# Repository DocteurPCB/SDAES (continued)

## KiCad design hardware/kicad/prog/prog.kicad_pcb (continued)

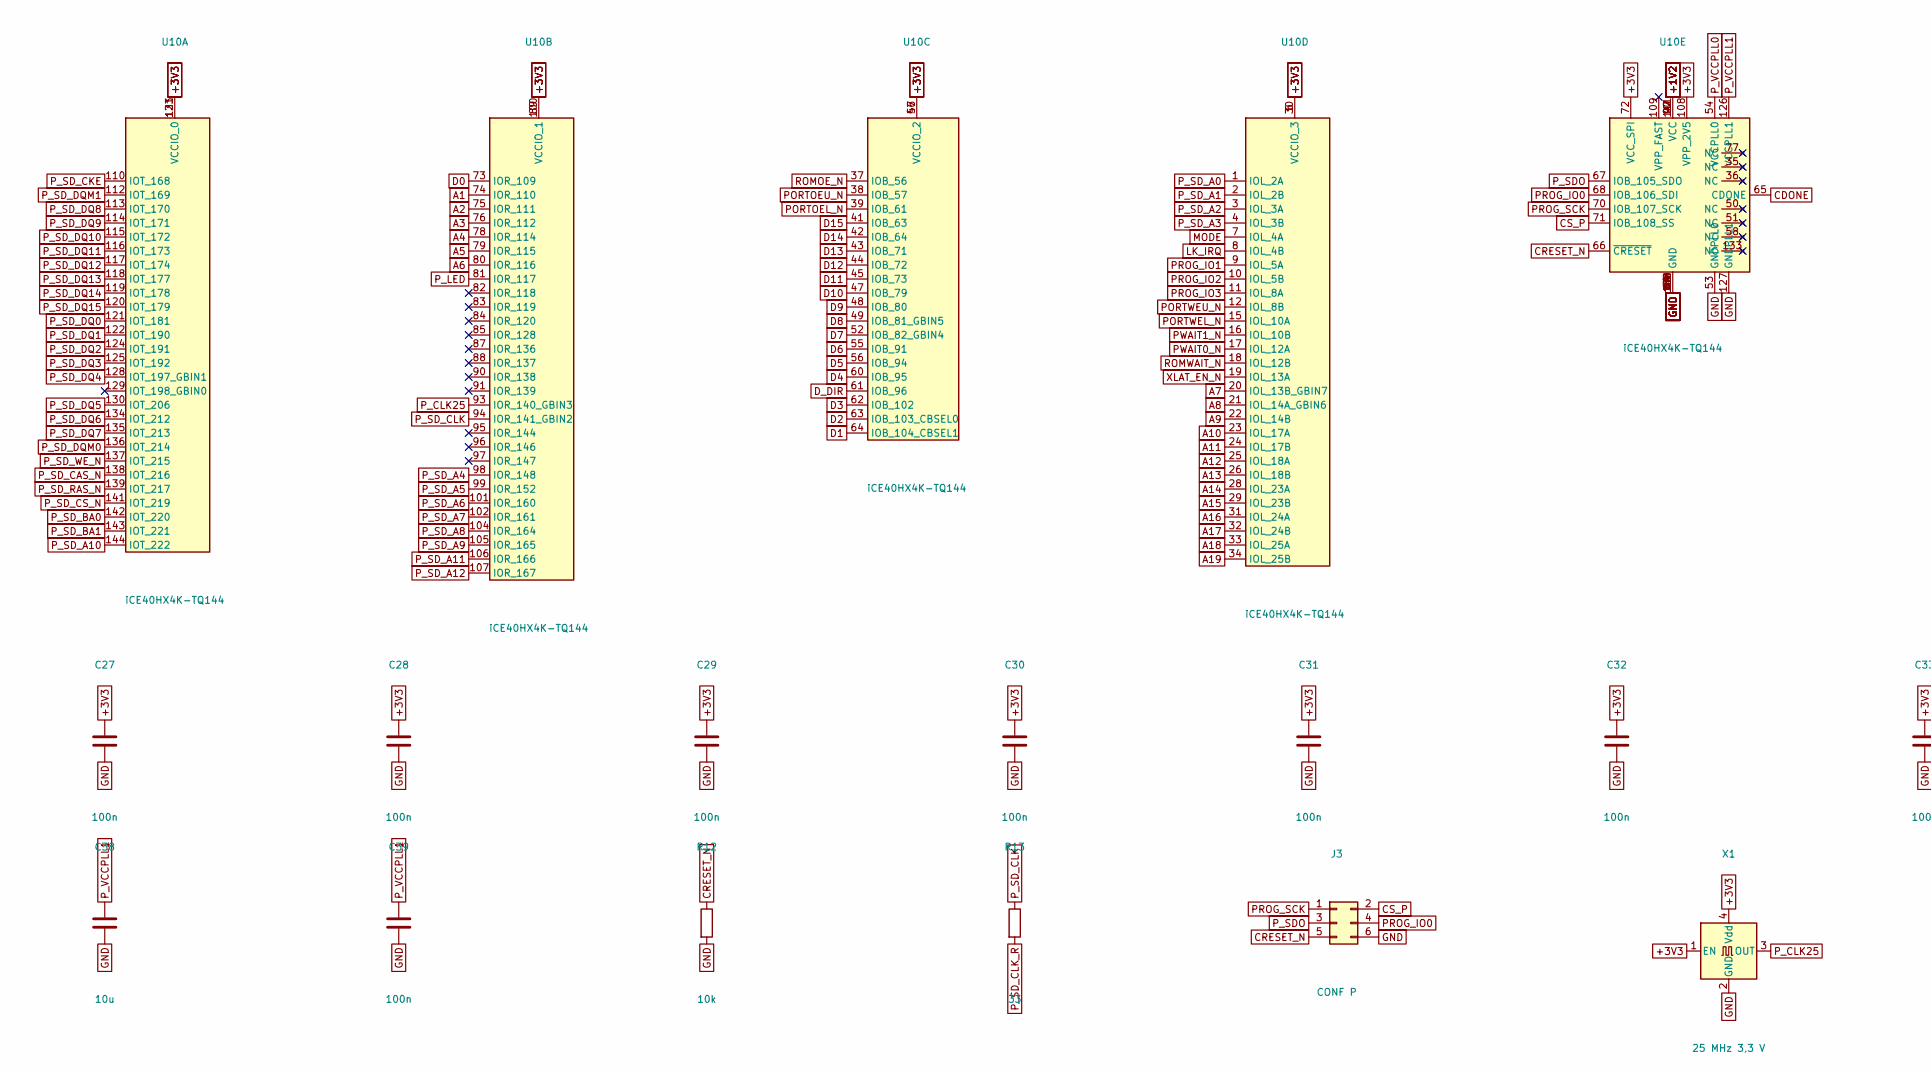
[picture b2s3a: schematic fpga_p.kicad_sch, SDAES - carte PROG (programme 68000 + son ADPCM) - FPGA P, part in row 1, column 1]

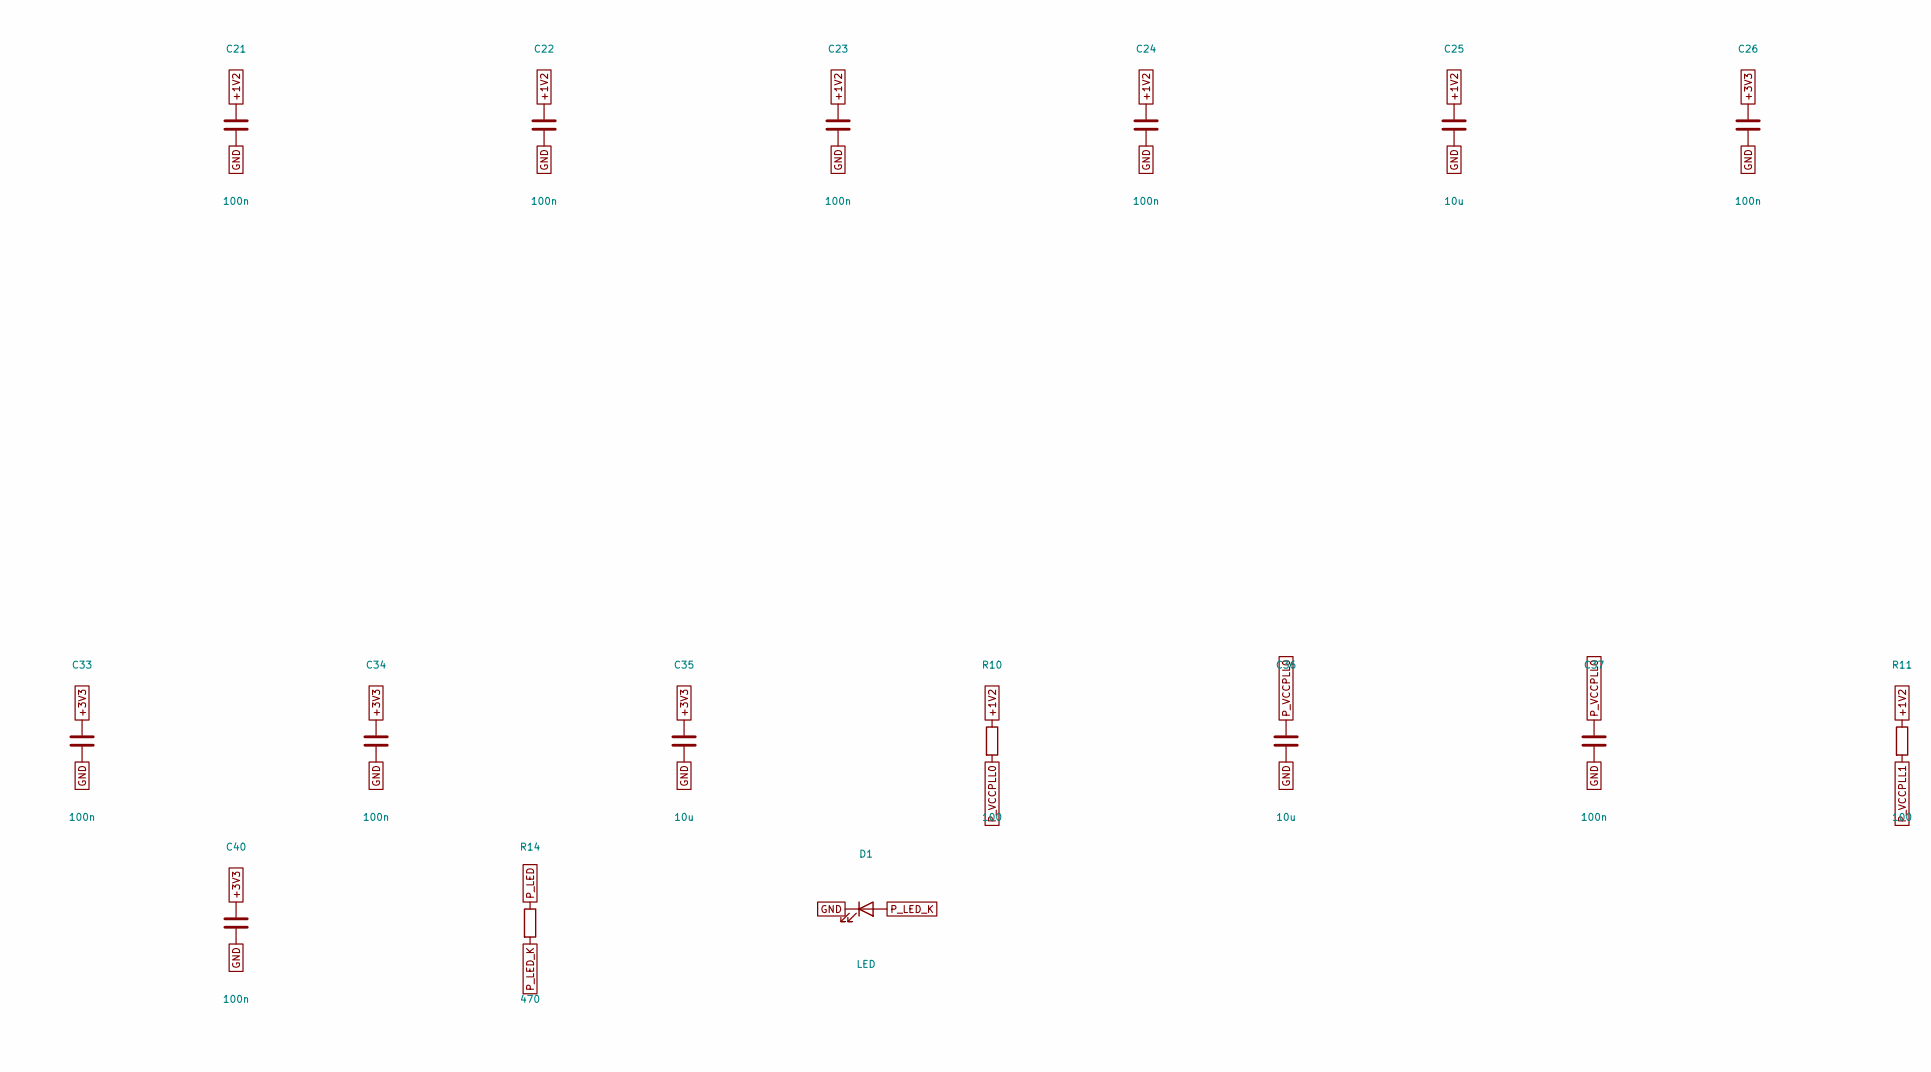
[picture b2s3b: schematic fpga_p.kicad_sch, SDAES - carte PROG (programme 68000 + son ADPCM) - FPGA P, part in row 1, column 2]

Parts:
C21, C22, C23, C24, C26, C27, C28, C29, C30, C31, C32, C33, C34, C37, C39, C40: 100n; C_0603_1608Metric
C25, C35, C36, C38: 10u; C_0805_2012Metric
D1: LED; LED_0603_1608Metric
J3: CONF P; PinHeader_2x03_P2.54mm_Vertical
R10, R11: 100; R_0603_1608Metric
R12: 10k; R_0603_1608Metric
R13: 33; R_0603_1608Metric
R14: 470; R_0603_1608Metric
U10: iCE40HX4K-TQ144; TQFP-144_20x20mm_P0.5mm
X1: 25 MHz 3,3 V; Oscillator_SMD_Abracon_ASE-4Pin_3.2x2.5mm_HandSoldering

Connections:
+1V2: C21.1, C22.1, C23.1, C24.1, C25.1, R10.1, R11.1, U10.27 (VCC), U10.40 (VCC), U10.92 (VCC), U10.111 (VCC); also elsewhere on the board
+3V3: C26.1, C27.1, C28.1, C29.1, C30.1, C31.1, C32.1, C33.1, C34.1, C35.1, C40.1, U10.6 (VCCIO_3), U10.30 (VCCIO_3), U10.46 (VCCIO_2), U10.57 (VCCIO_2), U10.72 (VCC_SPI), U10.89 (VCCIO_1), U10.100 (VCCIO_1), U10.108 (VPP_2V5), U10.123 (VCCIO_0), U10.131 (VCCIO_0), X1.1 (EN), X1.4 (Vdd); also elsewhere on the board
A1: U10.74 (IOR_110); also elsewhere on the board
A2: U10.75 (IOR_111); also elsewhere on the board
A3: U10.76 (IOR_112); also elsewhere on the board
A4: U10.78 (IOR_114); also elsewhere on the board
A5: U10.79 (IOR_115); also elsewhere on the board
A6: U10.80 (IOR_116); also elsewhere on the board
A7: U10.20 (IOL_13B_GBIN7); also elsewhere on the board
A8: U10.21 (IOL_14A_GBIN6); also elsewhere on the board
A9: U10.22 (IOL_14B); also elsewhere on the board
A10: U10.23 (IOL_17A); also elsewhere on the board
A11: U10.24 (IOL_17B); also elsewhere on the board
A12: U10.25 (IOL_18A); also elsewhere on the board
A13: U10.26 (IOL_18B); also elsewhere on the board
A14: U10.28 (IOL_23A); also elsewhere on the board
A15: U10.29 (IOL_23B); also elsewhere on the board
A16: U10.31 (IOL_24A); also elsewhere on the board
A17: U10.32 (IOL_24B); also elsewhere on the board
A18: U10.33 (IOL_25A); also elsewhere on the board
A19: U10.34 (IOL_25B); also elsewhere on the board
CDONE: U10.65 (CDONE); also elsewhere on the board
CRESET_N: J3.5, R12.1, U10.66 (~CRESET); also elsewhere on the board
CS_P: J3.2, U10.71 (IOB_108_SS); also elsewhere on the board
D0: U10.73 (IOR_109); also elsewhere on the board
D1: U10.64 (IOB_104_CBSEL1); also elsewhere on the board
D2: U10.63 (IOB_103_CBSEL0); also elsewhere on the board
D3: U10.62 (IOB_102); also elsewhere on the board
D4: U10.60 (IOB_95); also elsewhere on the board
D5: U10.56 (IOB_94); also elsewhere on the board
D6: U10.55 (IOB_91); also elsewhere on the board
D7: U10.52 (IOB_82_GBIN4); also elsewhere on the board
D8: U10.49 (IOB_81_GBIN5); also elsewhere on the board
D9: U10.48 (IOB_80); also elsewhere on the board
D10: U10.47 (IOB_79); also elsewhere on the board
D11: U10.45 (IOB_73); also elsewhere on the board
D12: U10.44 (IOB_72); also elsewhere on the board
D13: U10.43 (IOB_71); also elsewhere on the board
D14: U10.42 (IOB_64); also elsewhere on the board
D15: U10.41 (IOB_63); also elsewhere on the board
D_DIR: U10.61 (IOB_96); also elsewhere on the board
GND: C21.2, C22.2, C23.2, C24.2, C25.2, C26.2, C27.2, C28.2, C29.2, C30.2, C31.2, C32.2, C33.2, C34.2, C35.2, C36.2, C37.2, C38.2, C39.2, C40.2, D1.1 (K), J3.6, R12.2, U10.5 (GND), U10.13 (GND), U10.14 (GND), U10.53 (GNDPLL0), U10.59 (GND), U10.69 (GND), U10.86 (GND), U10.103 (GND), U10.127 (GNDPLL1), U10.132 (GND), U10.140 (GND), X1.2 (GND); also elsewhere on the board
LK_IRQ: U10.8 (IOL_4B); also elsewhere on the board
MODE: U10.7 (IOL_4A); also elsewhere on the board
PORTOEL_N: U10.39 (IOB_61); also elsewhere on the board
PORTOEU_N: U10.38 (IOB_57); also elsewhere on the board
PORTWEL_N: U10.15 (IOL_10A); also elsewhere on the board
PORTWEU_N: U10.12 (IOL_8B); also elsewhere on the board
PROG_IO0: J3.4, U10.68 (IOB_106_SDI); also elsewhere on the board
PROG_IO1: U10.9 (IOL_5A); also elsewhere on the board
PROG_IO2: U10.10 (IOL_5B); also elsewhere on the board
PROG_IO3: U10.11 (IOL_8A); also elsewhere on the board
PROG_SCK: J3.1, U10.70 (IOB_107_SCK); also elsewhere on the board
PWAIT0_N: U10.17 (IOL_12A); also elsewhere on the board
PWAIT1_N: U10.16 (IOL_10B); also elsewhere on the board
P_CLK25: U10.93 (IOR_140_GBIN3), X1.3 (OUT)
P_LED: R14.1, U10.81 (IOR_117)
P_LED_K: D1.2 (A), R14.2
P_SDO: J3.3, U10.67 (IOB_105_SDO)
P_SD_A0: U10.1 (IOL_2A); also elsewhere on the board
P_SD_A1: U10.2 (IOL_2B); also elsewhere on the board
P_SD_A2: U10.3 (IOL_3A); also elsewhere on the board
P_SD_A3: U10.4 (IOL_3B); also elsewhere on the board
P_SD_A4: U10.98 (IOR_148); also elsewhere on the board
P_SD_A5: U10.99 (IOR_152); also elsewhere on the board
P_SD_A6: U10.101 (IOR_160); also elsewhere on the board
P_SD_A7: U10.102 (IOR_161); also elsewhere on the board
P_SD_A8: U10.104 (IOR_164); also elsewhere on the board
P_SD_A9: U10.105 (IOR_165); also elsewhere on the board
P_SD_A10: U10.144 (IOT_222); also elsewhere on the board
P_SD_A11: U10.106 (IOR_166); also elsewhere on the board
P_SD_A12: U10.107 (IOR_167); also elsewhere on the board
P_SD_BA0: U10.142 (IOT_220); also elsewhere on the board
P_SD_BA1: U10.143 (IOT_221); also elsewhere on the board
P_SD_CAS_N: U10.138 (IOT_216); also elsewhere on the board
P_SD_CKE: U10.110 (IOT_168); also elsewhere on the board
P_SD_CLK: R13.1, U10.94 (IOR_141_GBIN2)
P_SD_CLK_R: R13.2; also elsewhere on the board
P_SD_CS_N: U10.141 (IOT_219); also elsewhere on the board
P_SD_DQ0: U10.121 (IOT_181); also elsewhere on the board
P_SD_DQ1: U10.122 (IOT_190); also elsewhere on the board
P_SD_DQ2: U10.124 (IOT_191); also elsewhere on the board
P_SD_DQ3: U10.125 (IOT_192); also elsewhere on the board
P_SD_DQ4: U10.128 (IOT_197_GBIN1); also elsewhere on the board
P_SD_DQ5: U10.130 (IOT_206); also elsewhere on the board
P_SD_DQ6: U10.134 (IOT_212); also elsewhere on the board
P_SD_DQ7: U10.135 (IOT_213); also elsewhere on the board
P_SD_DQ8: U10.113 (IOT_170); also elsewhere on the board
P_SD_DQ9: U10.114 (IOT_171); also elsewhere on the board
P_SD_DQ10: U10.115 (IOT_172); also elsewhere on the board
P_SD_DQ11: U10.116 (IOT_173); also elsewhere on the board
P_SD_DQ12: U10.117 (IOT_174); also elsewhere on the board
P_SD_DQ13: U10.118 (IOT_177); also elsewhere on the board
P_SD_DQ14: U10.119 (IOT_178); also elsewhere on the board
P_SD_DQ15: U10.120 (IOT_179); also elsewhere on the board
P_SD_DQM0: U10.136 (IOT_214); also elsewhere on the board
P_SD_DQM1: U10.112 (IOT_169); also elsewhere on the board
P_SD_RAS_N: U10.139 (IOT_217); also elsewhere on the board
P_SD_WE_N: U10.137 (IOT_215); also elsewhere on the board
P_VCCPLL0: C36.1, C37.1, R10.2, U10.54 (VCCPLL0)
P_VCCPLL1: C38.1, C39.1, R11.2, U10.126 (VCCPLL1)
ROMOE_N: U10.37 (IOB_56); also elsewhere on the board
ROMWAIT_N: U10.18 (IOL_12B); also elsewhere on the board
XLAT_EN_N: U10.19 (IOL_13A); also elsewhere on the board

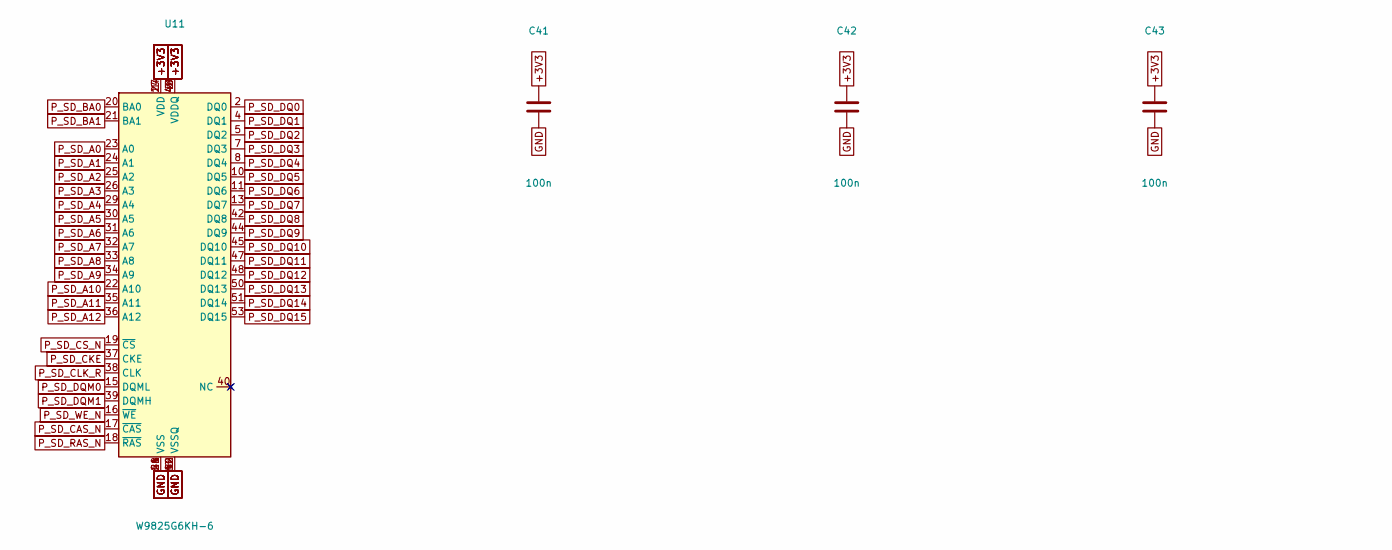
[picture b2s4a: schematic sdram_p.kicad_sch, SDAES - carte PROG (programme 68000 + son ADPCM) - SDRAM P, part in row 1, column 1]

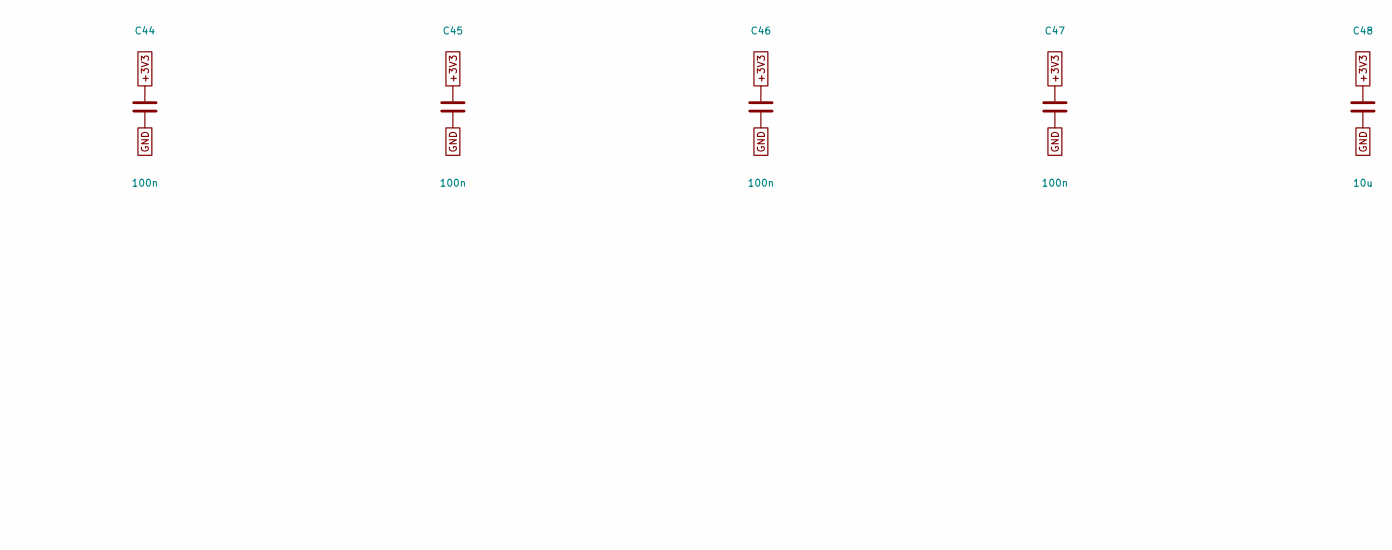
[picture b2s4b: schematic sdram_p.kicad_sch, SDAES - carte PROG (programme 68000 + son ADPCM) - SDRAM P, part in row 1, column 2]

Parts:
C41, C42, C43, C44, C45, C46, C47: 100n; C_0603_1608Metric
C48: 10u; C_0805_2012Metric
U11: W9825G6KH-6; TSOP-II-54_22.2x10.16mm_P0.8mm

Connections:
+3V3: C41.1, C42.1, C43.1, C44.1, C45.1, C46.1, C47.1, C48.1, U11.1 (VDD), U11.3 (VDDQ), U11.9 (VDDQ), U11.14 (VDD), U11.27 (VDD), U11.43 (VDDQ), U11.49 (VDDQ); also elsewhere on the board
GND: C41.2, C42.2, C43.2, C44.2, C45.2, C46.2, C47.2, C48.2, U11.6 (VSSQ), U11.12 (VSSQ), U11.28 (VSS), U11.41 (VSS), U11.46 (VSSQ), U11.52 (VSSQ), U11.54 (VSS); also elsewhere on the board
P_SD_A0: U11.23 (A0); also elsewhere on the board
P_SD_A1: U11.24 (A1); also elsewhere on the board
P_SD_A2: U11.25 (A2); also elsewhere on the board
P_SD_A3: U11.26 (A3); also elsewhere on the board
P_SD_A4: U11.29 (A4); also elsewhere on the board
P_SD_A5: U11.30 (A5); also elsewhere on the board
P_SD_A6: U11.31 (A6); also elsewhere on the board
P_SD_A7: U11.32 (A7); also elsewhere on the board
P_SD_A8: U11.33 (A8); also elsewhere on the board
P_SD_A9: U11.34 (A9); also elsewhere on the board
P_SD_A10: U11.22 (A10); also elsewhere on the board
P_SD_A11: U11.35 (A11); also elsewhere on the board
P_SD_A12: U11.36 (A12); also elsewhere on the board
P_SD_BA0: U11.20 (BA0); also elsewhere on the board
P_SD_BA1: U11.21 (BA1); also elsewhere on the board
P_SD_CAS_N: U11.17 (~CAS); also elsewhere on the board
P_SD_CKE: U11.37 (CKE); also elsewhere on the board
P_SD_CLK_R: U11.38 (CLK); also elsewhere on the board
P_SD_CS_N: U11.19 (~CS); also elsewhere on the board
P_SD_DQ0: U11.2 (DQ0); also elsewhere on the board
P_SD_DQ1: U11.4 (DQ1); also elsewhere on the board
P_SD_DQ2: U11.5 (DQ2); also elsewhere on the board
P_SD_DQ3: U11.7 (DQ3); also elsewhere on the board
P_SD_DQ4: U11.8 (DQ4); also elsewhere on the board
P_SD_DQ5: U11.10 (DQ5); also elsewhere on the board
P_SD_DQ6: U11.11 (DQ6); also elsewhere on the board
P_SD_DQ7: U11.13 (DQ7); also elsewhere on the board
P_SD_DQ8: U11.42 (DQ8); also elsewhere on the board
P_SD_DQ9: U11.44 (DQ9); also elsewhere on the board
P_SD_DQ10: U11.45 (DQ10); also elsewhere on the board
P_SD_DQ11: U11.47 (DQ11); also elsewhere on the board
P_SD_DQ12: U11.48 (DQ12); also elsewhere on the board
P_SD_DQ13: U11.50 (DQ13); also elsewhere on the board
P_SD_DQ14: U11.51 (DQ14); also elsewhere on the board
P_SD_DQ15: U11.53 (DQ15); also elsewhere on the board
P_SD_DQM0: U11.15 (DQML); also elsewhere on the board
P_SD_DQM1: U11.39 (DQMH); also elsewhere on the board
P_SD_RAS_N: U11.18 (~RAS); also elsewhere on the board
P_SD_WE_N: U11.16 (~WE); also elsewhere on the board

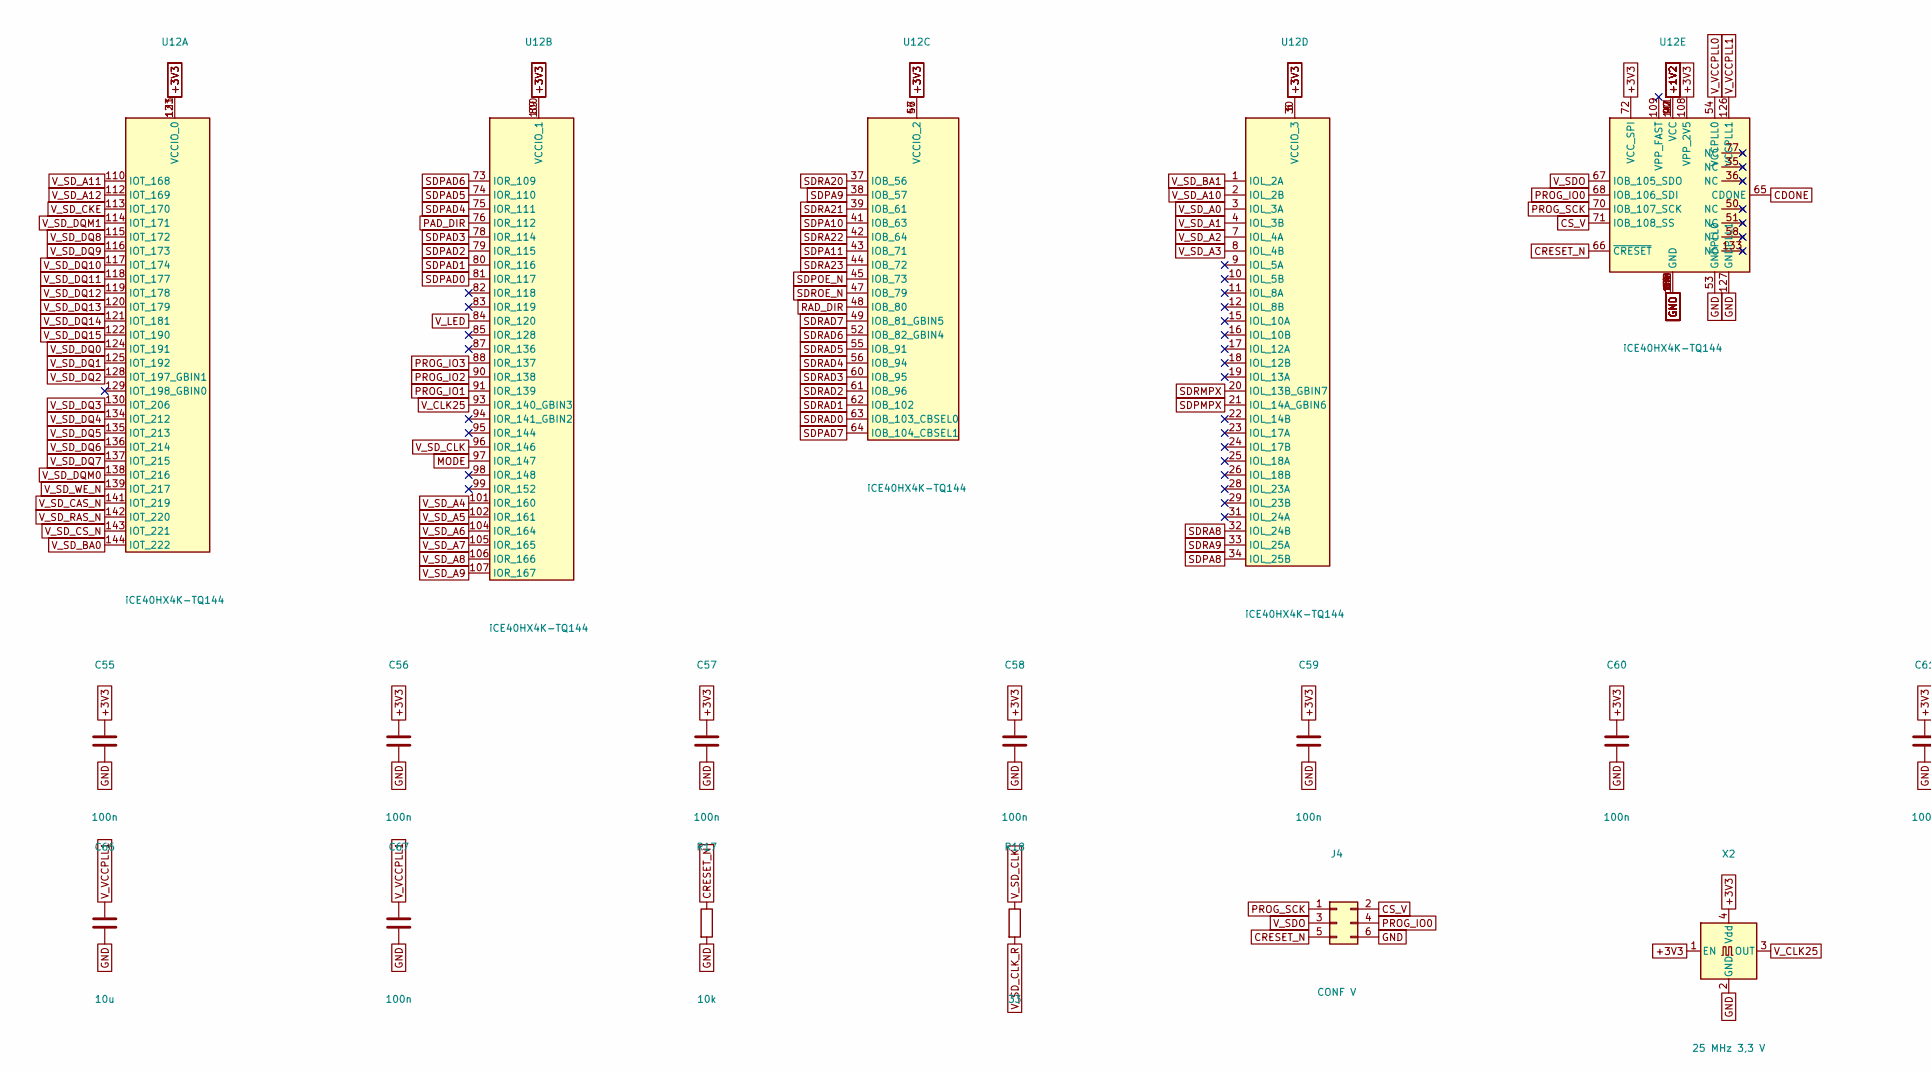
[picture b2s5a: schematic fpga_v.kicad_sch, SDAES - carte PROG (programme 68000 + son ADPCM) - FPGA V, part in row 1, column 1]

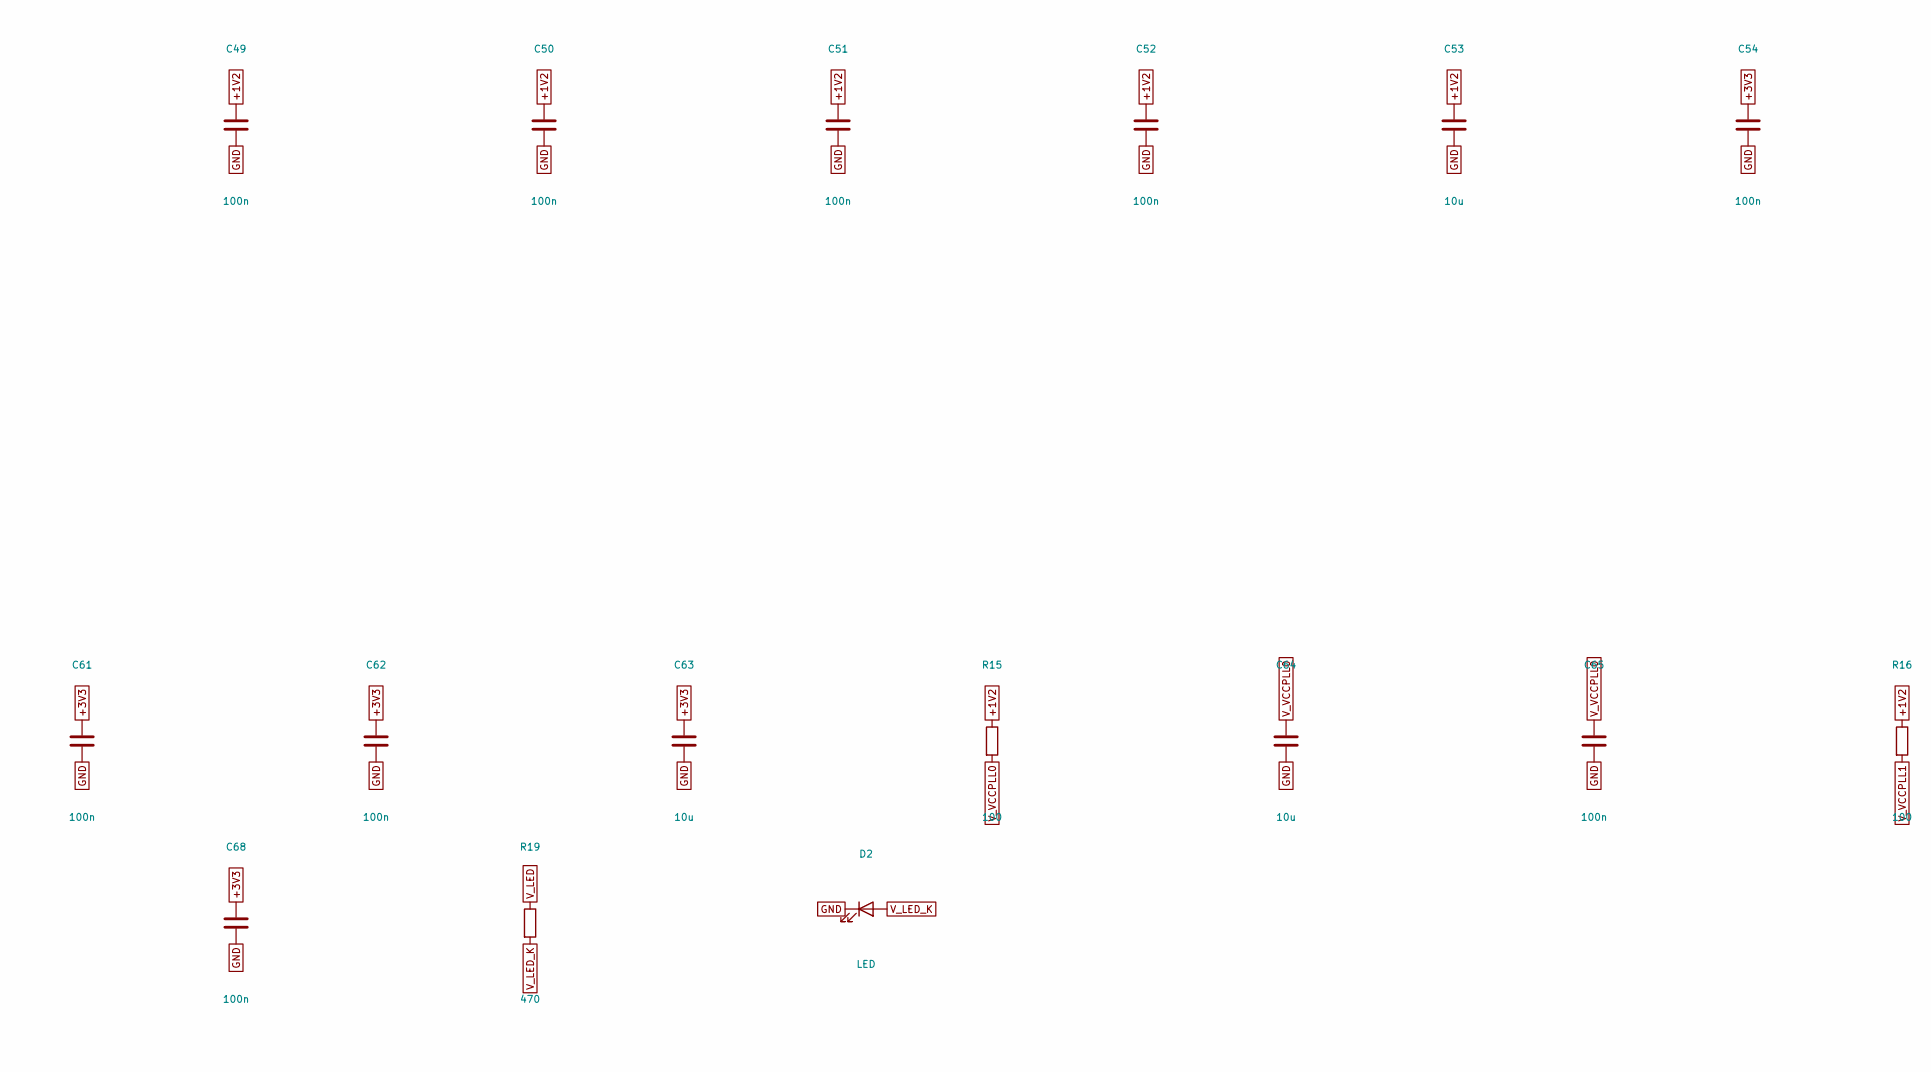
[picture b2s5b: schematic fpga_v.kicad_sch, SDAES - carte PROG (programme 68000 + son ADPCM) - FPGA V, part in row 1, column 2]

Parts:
C49, C50, C51, C52, C54, C55, C56, C57, C58, C59, C60, C61, C62, C65, C67, C68: 100n; C_0603_1608Metric
C53, C63, C64, C66: 10u; C_0805_2012Metric
D2: LED; LED_0603_1608Metric
J4: CONF V; PinHeader_2x03_P2.54mm_Vertical
R15, R16: 100; R_0603_1608Metric
R17: 10k; R_0603_1608Metric
R18: 33; R_0603_1608Metric
R19: 470; R_0603_1608Metric
U12: iCE40HX4K-TQ144; TQFP-144_20x20mm_P0.5mm
X2: 25 MHz 3,3 V; Oscillator_SMD_Abracon_ASE-4Pin_3.2x2.5mm_HandSoldering

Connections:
+1V2: C49.1, C50.1, C51.1, C52.1, C53.1, R15.1, R16.1, U12.27 (VCC), U12.40 (VCC), U12.92 (VCC), U12.111 (VCC); also elsewhere on the board
+3V3: C54.1, C55.1, C56.1, C57.1, C58.1, C59.1, C60.1, C61.1, C62.1, C63.1, C68.1, U12.6 (VCCIO_3), U12.30 (VCCIO_3), U12.46 (VCCIO_2), U12.57 (VCCIO_2), U12.72 (VCC_SPI), U12.89 (VCCIO_1), U12.100 (VCCIO_1), U12.108 (VPP_2V5), U12.123 (VCCIO_0), U12.131 (VCCIO_0), X2.1 (EN), X2.4 (Vdd); also elsewhere on the board
CDONE: U12.65 (CDONE); also elsewhere on the board
CRESET_N: J4.5, R17.1, U12.66 (~CRESET); also elsewhere on the board
CS_V: J4.2, U12.71 (IOB_108_SS); also elsewhere on the board
GND: C49.2, C50.2, C51.2, C52.2, C53.2, C54.2, C55.2, C56.2, C57.2, C58.2, C59.2, C60.2, C61.2, C62.2, C63.2, C64.2, C65.2, C66.2, C67.2, C68.2, D2.1 (K), J4.6, R17.2, U12.5 (GND), U12.13 (GND), U12.14 (GND), U12.53 (GNDPLL0), U12.59 (GND), U12.69 (GND), U12.86 (GND), U12.103 (GND), U12.127 (GNDPLL1), U12.132 (GND), U12.140 (GND), X2.2 (GND); also elsewhere on the board
MODE: U12.97 (IOR_147); also elsewhere on the board
PAD_DIR: U12.76 (IOR_112); also elsewhere on the board
PROG_IO0: J4.4, U12.68 (IOB_106_SDI); also elsewhere on the board
PROG_IO1: U12.91 (IOR_139); also elsewhere on the board
PROG_IO2: U12.90 (IOR_138); also elsewhere on the board
PROG_IO3: U12.88 (IOR_137); also elsewhere on the board
PROG_SCK: J4.1, U12.70 (IOB_107_SCK); also elsewhere on the board
RAD_DIR: U12.48 (IOB_80); also elsewhere on the board
SDPA8: U12.34 (IOL_25B); also elsewhere on the board
SDPA9: U12.38 (IOB_57); also elsewhere on the board
SDPA10: U12.41 (IOB_63); also elsewhere on the board
SDPA11: U12.43 (IOB_71); also elsewhere on the board
SDPAD0: U12.81 (IOR_117); also elsewhere on the board
SDPAD1: U12.80 (IOR_116); also elsewhere on the board
SDPAD2: U12.79 (IOR_115); also elsewhere on the board
SDPAD3: U12.78 (IOR_114); also elsewhere on the board
SDPAD4: U12.75 (IOR_111); also elsewhere on the board
SDPAD5: U12.74 (IOR_110); also elsewhere on the board
SDPAD6: U12.73 (IOR_109); also elsewhere on the board
SDPAD7: U12.64 (IOB_104_CBSEL1); also elsewhere on the board
SDPMPX: U12.21 (IOL_14A_GBIN6); also elsewhere on the board
SDPOE_N: U12.45 (IOB_73); also elsewhere on the board
SDRA8: U12.32 (IOL_24B); also elsewhere on the board
SDRA9: U12.33 (IOL_25A); also elsewhere on the board
SDRA20: U12.37 (IOB_56); also elsewhere on the board
SDRA21: U12.39 (IOB_61); also elsewhere on the board
SDRA22: U12.42 (IOB_64); also elsewhere on the board
SDRA23: U12.44 (IOB_72); also elsewhere on the board
SDRAD0: U12.63 (IOB_103_CBSEL0); also elsewhere on the board
SDRAD1: U12.62 (IOB_102); also elsewhere on the board
SDRAD2: U12.61 (IOB_96); also elsewhere on the board
SDRAD3: U12.60 (IOB_95); also elsewhere on the board
SDRAD4: U12.56 (IOB_94); also elsewhere on the board
SDRAD5: U12.55 (IOB_91); also elsewhere on the board
SDRAD6: U12.52 (IOB_82_GBIN4); also elsewhere on the board
SDRAD7: U12.49 (IOB_81_GBIN5); also elsewhere on the board
SDRMPX: U12.20 (IOL_13B_GBIN7); also elsewhere on the board
SDROE_N: U12.47 (IOB_79); also elsewhere on the board
V_CLK25: U12.93 (IOR_140_GBIN3), X2.3 (OUT)
V_LED: R19.1, U12.84 (IOR_120)
V_LED_K: D2.2 (A), R19.2
V_SDO: J4.3, U12.67 (IOB_105_SDO)
V_SD_A0: U12.3 (IOL_3A); also elsewhere on the board
V_SD_A1: U12.4 (IOL_3B); also elsewhere on the board
V_SD_A2: U12.7 (IOL_4A); also elsewhere on the board
V_SD_A3: U12.8 (IOL_4B); also elsewhere on the board
V_SD_A4: U12.101 (IOR_160); also elsewhere on the board
V_SD_A5: U12.102 (IOR_161); also elsewhere on the board
V_SD_A6: U12.104 (IOR_164); also elsewhere on the board
V_SD_A7: U12.105 (IOR_165); also elsewhere on the board
V_SD_A8: U12.106 (IOR_166); also elsewhere on the board
V_SD_A9: U12.107 (IOR_167); also elsewhere on the board
V_SD_A10: U12.2 (IOL_2B); also elsewhere on the board
V_SD_A11: U12.110 (IOT_168); also elsewhere on the board
V_SD_A12: U12.112 (IOT_169); also elsewhere on the board
V_SD_BA0: U12.144 (IOT_222); also elsewhere on the board
V_SD_BA1: U12.1 (IOL_2A); also elsewhere on the board
V_SD_CAS_N: U12.141 (IOT_219); also elsewhere on the board
V_SD_CKE: U12.113 (IOT_170); also elsewhere on the board
V_SD_CLK: R18.1, U12.96 (IOR_146)
V_SD_CLK_R: R18.2; also elsewhere on the board
V_SD_CS_N: U12.143 (IOT_221); also elsewhere on the board
V_SD_DQ0: U12.124 (IOT_191); also elsewhere on the board
V_SD_DQ1: U12.125 (IOT_192); also elsewhere on the board
V_SD_DQ2: U12.128 (IOT_197_GBIN1); also elsewhere on the board
V_SD_DQ3: U12.130 (IOT_206); also elsewhere on the board
V_SD_DQ4: U12.134 (IOT_212); also elsewhere on the board
V_SD_DQ5: U12.135 (IOT_213); also elsewhere on the board
V_SD_DQ6: U12.136 (IOT_214); also elsewhere on the board
V_SD_DQ7: U12.137 (IOT_215); also elsewhere on the board
V_SD_DQ8: U12.115 (IOT_172); also elsewhere on the board
V_SD_DQ9: U12.116 (IOT_173); also elsewhere on the board
V_SD_DQ10: U12.117 (IOT_174); also elsewhere on the board
V_SD_DQ11: U12.118 (IOT_177); also elsewhere on the board
V_SD_DQ12: U12.119 (IOT_178); also elsewhere on the board
V_SD_DQ13: U12.120 (IOT_179); also elsewhere on the board
V_SD_DQ14: U12.121 (IOT_181); also elsewhere on the board
V_SD_DQ15: U12.122 (IOT_190); also elsewhere on the board
V_SD_DQM0: U12.138 (IOT_216); also elsewhere on the board
V_SD_DQM1: U12.114 (IOT_171); also elsewhere on the board
V_SD_RAS_N: U12.142 (IOT_220); also elsewhere on the board
V_SD_WE_N: U12.139 (IOT_217); also elsewhere on the board
V_VCCPLL0: C64.1, C65.1, R15.2, U12.54 (VCCPLL0)
V_VCCPLL1: C66.1, C67.1, R16.2, U12.126 (VCCPLL1)

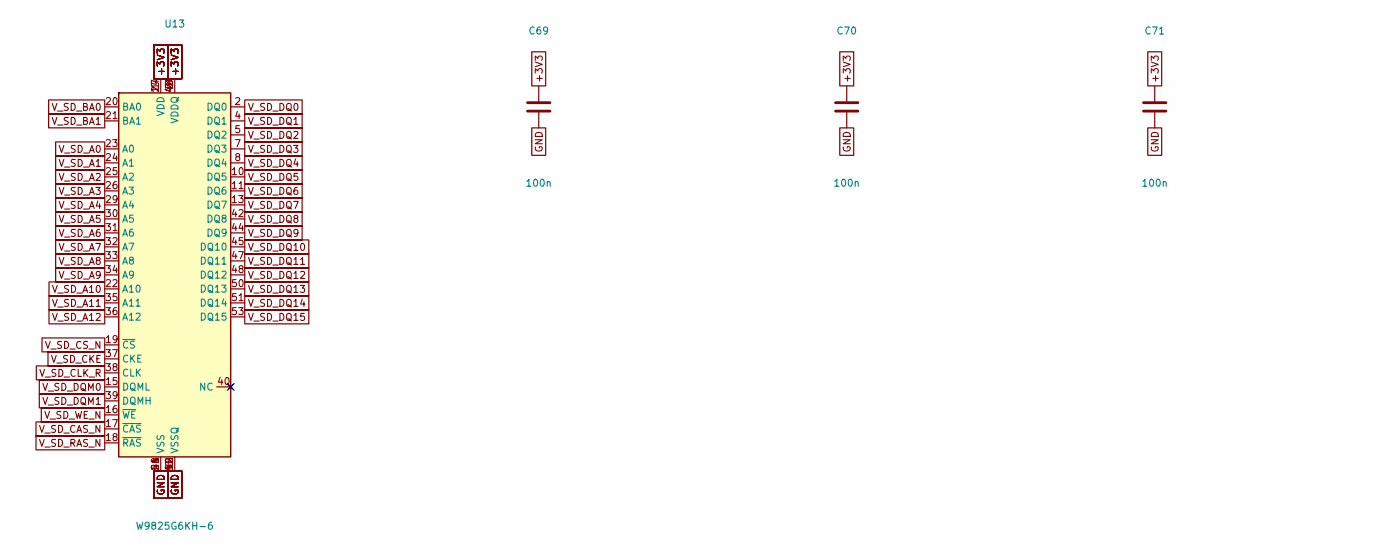
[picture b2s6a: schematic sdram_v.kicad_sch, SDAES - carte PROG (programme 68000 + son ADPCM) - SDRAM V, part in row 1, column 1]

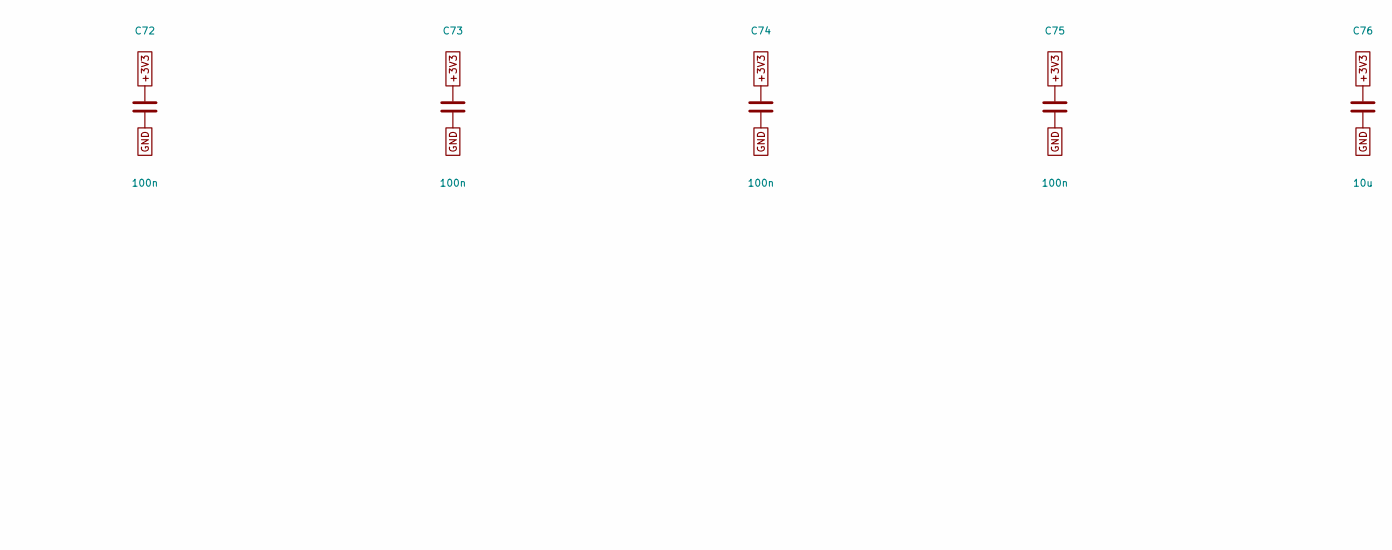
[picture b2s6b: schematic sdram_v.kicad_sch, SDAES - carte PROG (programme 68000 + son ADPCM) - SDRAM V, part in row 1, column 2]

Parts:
C69, C70, C71, C72, C73, C74, C75: 100n; C_0603_1608Metric
C76: 10u; C_0805_2012Metric
U13: W9825G6KH-6; TSOP-II-54_22.2x10.16mm_P0.8mm

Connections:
+3V3: C69.1, C70.1, C71.1, C72.1, C73.1, C74.1, C75.1, C76.1, U13.1 (VDD), U13.3 (VDDQ), U13.9 (VDDQ), U13.14 (VDD), U13.27 (VDD), U13.43 (VDDQ), U13.49 (VDDQ); also elsewhere on the board
GND: C69.2, C70.2, C71.2, C72.2, C73.2, C74.2, C75.2, C76.2, U13.6 (VSSQ), U13.12 (VSSQ), U13.28 (VSS), U13.41 (VSS), U13.46 (VSSQ), U13.52 (VSSQ), U13.54 (VSS); also elsewhere on the board
V_SD_A0: U13.23 (A0); also elsewhere on the board
V_SD_A1: U13.24 (A1); also elsewhere on the board
V_SD_A2: U13.25 (A2); also elsewhere on the board
V_SD_A3: U13.26 (A3); also elsewhere on the board
V_SD_A4: U13.29 (A4); also elsewhere on the board
V_SD_A5: U13.30 (A5); also elsewhere on the board
V_SD_A6: U13.31 (A6); also elsewhere on the board
V_SD_A7: U13.32 (A7); also elsewhere on the board
V_SD_A8: U13.33 (A8); also elsewhere on the board
V_SD_A9: U13.34 (A9); also elsewhere on the board
V_SD_A10: U13.22 (A10); also elsewhere on the board
V_SD_A11: U13.35 (A11); also elsewhere on the board
V_SD_A12: U13.36 (A12); also elsewhere on the board
V_SD_BA0: U13.20 (BA0); also elsewhere on the board
V_SD_BA1: U13.21 (BA1); also elsewhere on the board
V_SD_CAS_N: U13.17 (~CAS); also elsewhere on the board
V_SD_CKE: U13.37 (CKE); also elsewhere on the board
V_SD_CLK_R: U13.38 (CLK); also elsewhere on the board
V_SD_CS_N: U13.19 (~CS); also elsewhere on the board
V_SD_DQ0: U13.2 (DQ0); also elsewhere on the board
V_SD_DQ1: U13.4 (DQ1); also elsewhere on the board
V_SD_DQ2: U13.5 (DQ2); also elsewhere on the board
V_SD_DQ3: U13.7 (DQ3); also elsewhere on the board
V_SD_DQ4: U13.8 (DQ4); also elsewhere on the board
V_SD_DQ5: U13.10 (DQ5); also elsewhere on the board
V_SD_DQ6: U13.11 (DQ6); also elsewhere on the board
V_SD_DQ7: U13.13 (DQ7); also elsewhere on the board
V_SD_DQ8: U13.42 (DQ8); also elsewhere on the board
V_SD_DQ9: U13.44 (DQ9); also elsewhere on the board
V_SD_DQ10: U13.45 (DQ10); also elsewhere on the board
V_SD_DQ11: U13.47 (DQ11); also elsewhere on the board
V_SD_DQ12: U13.48 (DQ12); also elsewhere on the board
V_SD_DQ13: U13.50 (DQ13); also elsewhere on the board
V_SD_DQ14: U13.51 (DQ14); also elsewhere on the board
V_SD_DQ15: U13.53 (DQ15); also elsewhere on the board
V_SD_DQM0: U13.15 (DQML); also elsewhere on the board
V_SD_DQM1: U13.39 (DQMH); also elsewhere on the board
V_SD_RAS_N: U13.18 (~RAS); also elsewhere on the board
V_SD_WE_N: U13.16 (~WE); also elsewhere on the board
